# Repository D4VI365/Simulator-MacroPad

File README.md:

# Simulator-MacroPad

My project for the macropad contest of hackclub. It has 12 buttons as well as 1 rotary encoder with two leds which indicate the level of the encoder using colours.

I plan on using this pad to help me with my in-race adjustments, as well using it in other applications by mapping the buttons to do specific actions (like muting discord or actions of voicemod) or attaching more complex macros to them

BottomBox:

TopCover:

FullBox:

BottomBox+PCB:

Full Assemble:

PCB:

Wiring Schematic:

Completed Design:

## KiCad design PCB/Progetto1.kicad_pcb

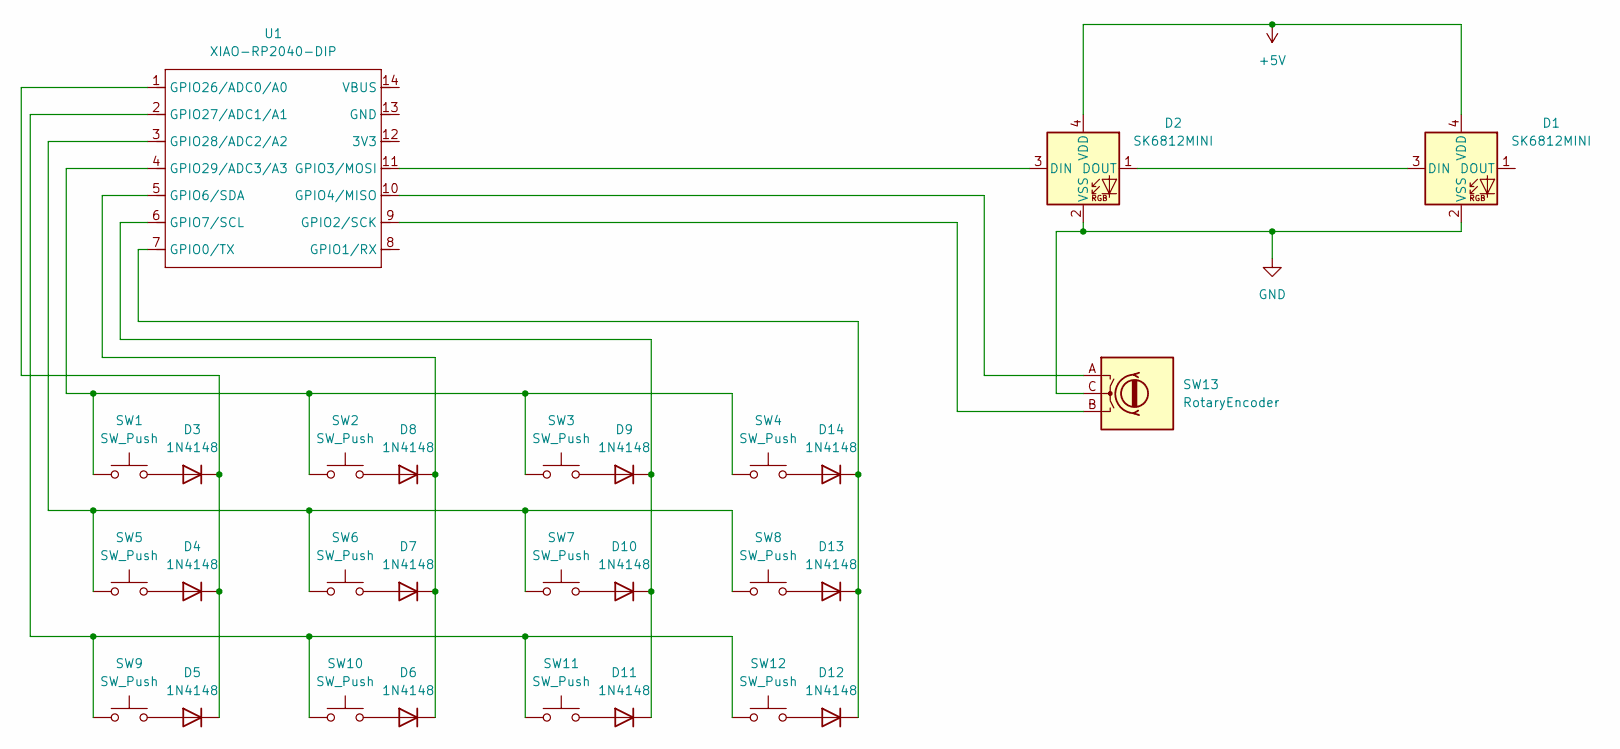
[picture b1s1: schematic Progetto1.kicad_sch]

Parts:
D1, D2: SK6812MINI; LED_SK6812MINI_PLCC4_3.5x3.5mm_P1.75mm
D3, D4, D5, D6, D7, D8, D9, D10, D11, D12, D13, D14: 1N4148; D_DO-35_SOD27_P7.62mm_Horizontal
SW1, SW2, SW3, SW4, SW5, SW6, SW7, SW8, SW9, SW10, SW11, SW12: SW_Push; SW_Cherry_MX_1.00u_PCB
SW13: RotaryEncoder; RotaryEncoder_Alps_EC11E-Switch_Vertical_H20mm
U1: XIAO-RP2040-DIP

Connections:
+5V: D1.4 (VDD), D2.4 (VDD)
GND: D1.2 (VSS), D2.2 (VSS), SW13.C
unnamed: D1.3 (DIN), D2.1 (DOUT)
unnamed: D2.3 (DIN), U1.11 (GPIO3/MOSI)
unnamed: D3.2 (A), SW1.2
unnamed: D3.1 (K), D4.1 (K), D5.1 (K), U1.1 (GPIO26/ADC0/A0)
unnamed: D4.2 (A), SW5.2
unnamed: D5.2 (A), SW9.2
unnamed: D6.2 (A), SW10.2
unnamed: D6.1 (K), D7.1 (K), D8.1 (K), U1.5 (GPIO6/SDA)
unnamed: D7.2 (A), SW6.2
unnamed: D8.2 (A), SW2.2
unnamed: D9.2 (A), SW3.2
unnamed: D10.2 (A), SW7.2
unnamed: D9.1 (K), D10.1 (K), D11.1 (K), U1.6 (GPIO7/SCL)
unnamed: D11.2 (A), SW11.2
unnamed: D12.2 (A), SW12.2
unnamed: D12.1 (K), D13.1 (K), D14.1 (K), U1.7 (GPIO0/TX)
unnamed: D13.2 (A), SW8.2
unnamed: D14.2 (A), SW4.2
unnamed: SW13.B, U1.9 (GPIO2/SCK)
unnamed: SW13.A, U1.10 (GPIO4/MISO)
unnamed: SW9.1, SW10.1, SW11.1, SW12.1, U1.2 (GPIO27/ADC1/A1)
unnamed: SW5.1, SW6.1, SW7.1, SW8.1, U1.3 (GPIO28/ADC2/A2)
unnamed: SW1.1, SW2.1, SW3.1, SW4.1, U1.4 (GPIO29/ADC3/A3)

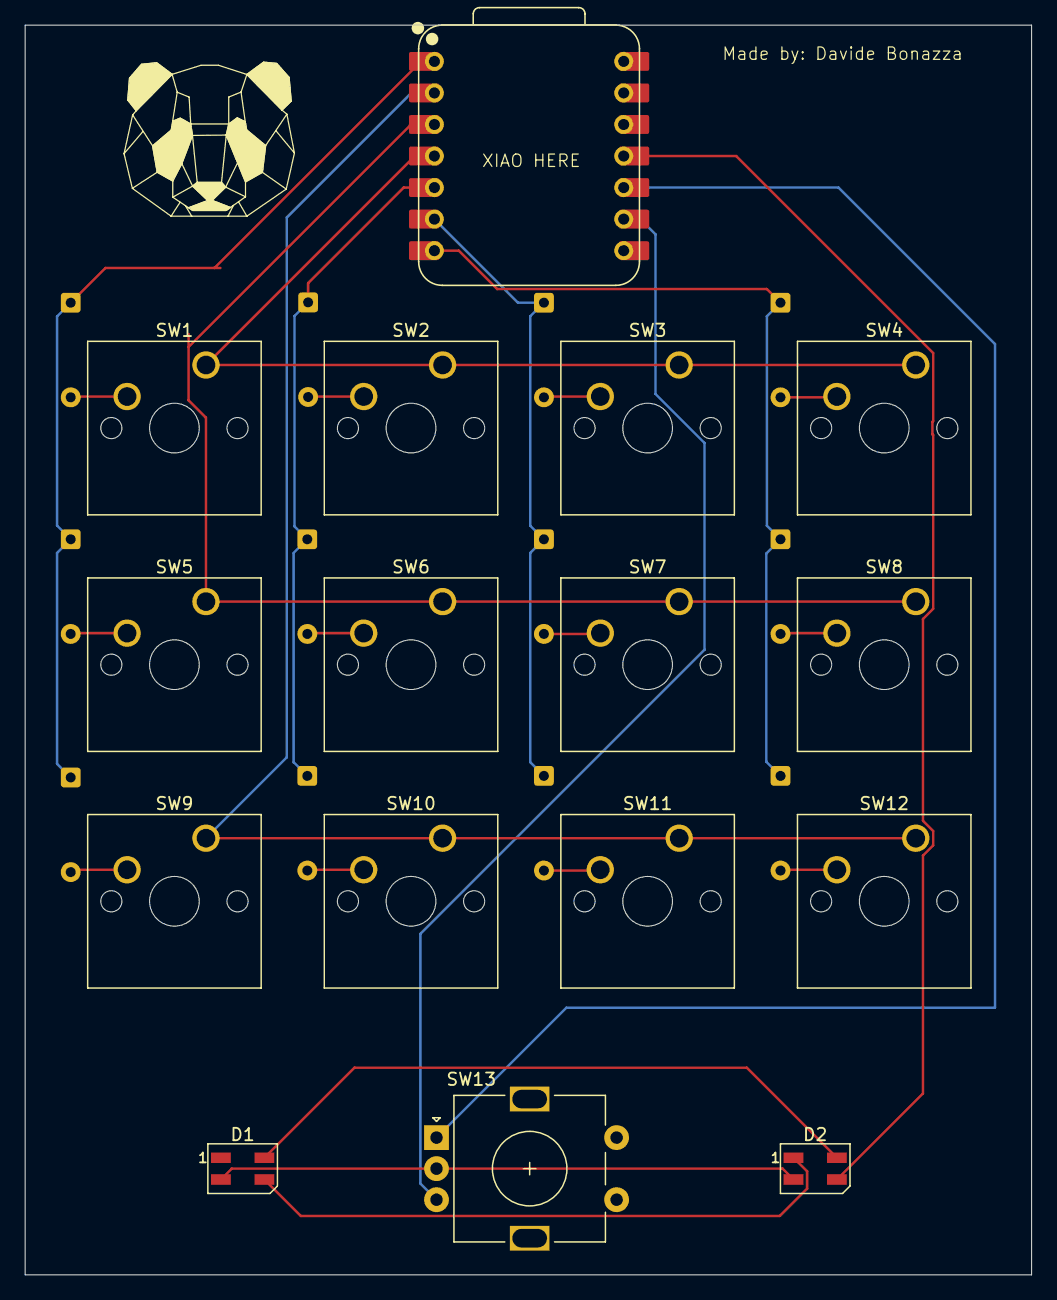
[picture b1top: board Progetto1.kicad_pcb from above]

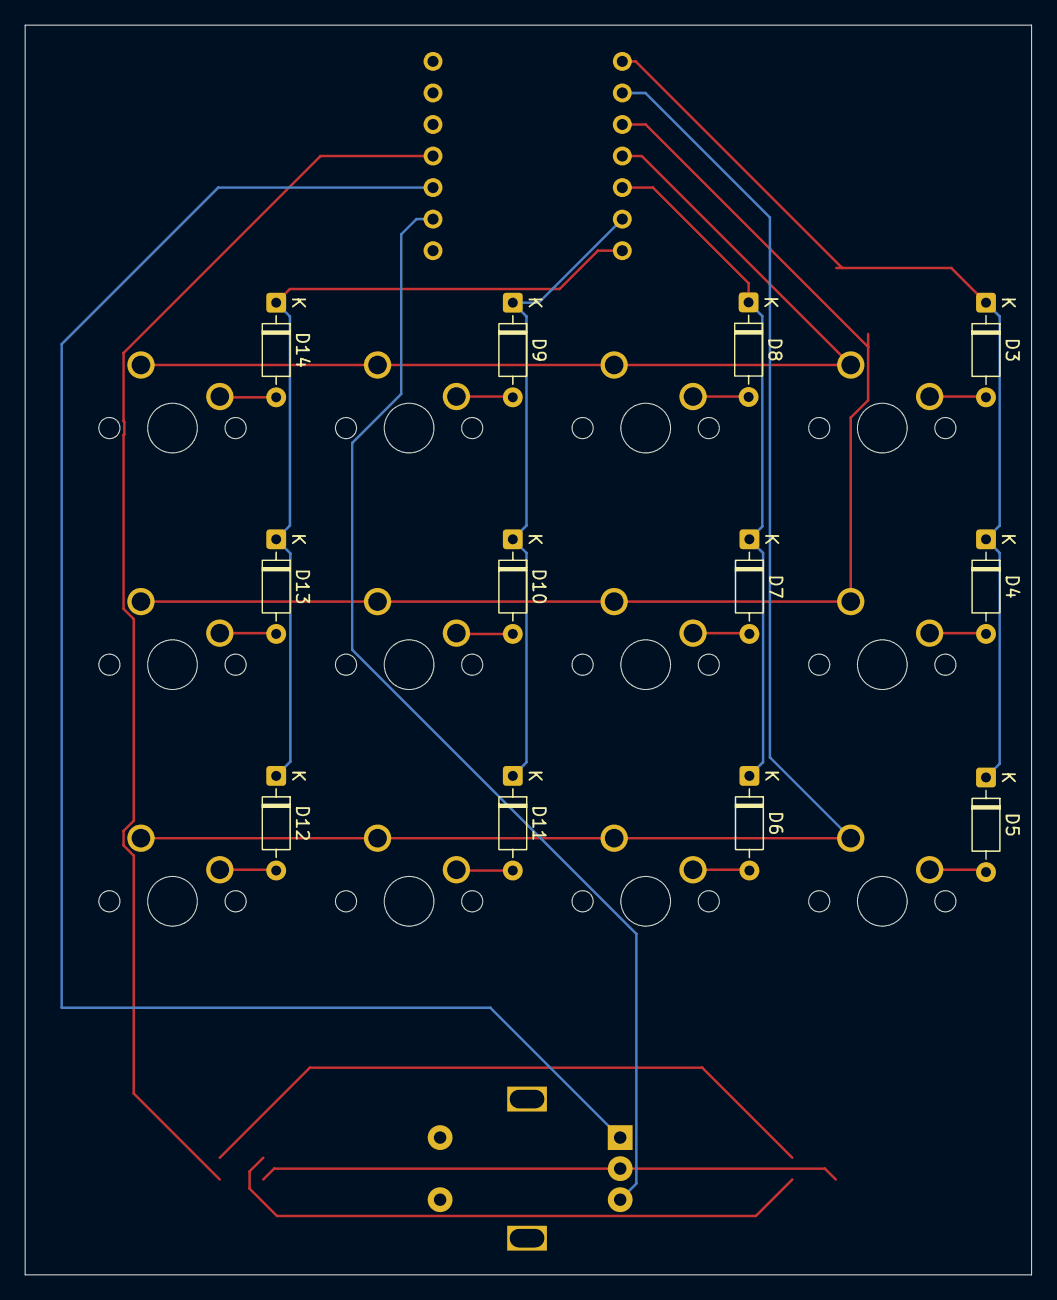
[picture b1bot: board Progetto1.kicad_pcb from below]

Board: 2 copper layers, 81.0 x 100.6 mm, 28 parts (12 on the bottom side), 25 nets.

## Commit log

2025-11-30 add README
2026-01-13 Refactor encoder handling and remove test script
    Deleted the obsolete 'Test led/code.py' test script. Moved encoder handling logic directly into the main loop in 'code.py', replacing the separate CheckEncoder function. Now, encoder rotation trigger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
2026-01-25 Update CAD files: add BottomBox and UpperFrame, remove frames
    Added BottomBox.step and UpperFrame.step to the CAD directory. Removed obsolete BottomFrame.stl and TopFrame.stl files. This updates the CAD models to the latest STEP format and removes outdated STL 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
